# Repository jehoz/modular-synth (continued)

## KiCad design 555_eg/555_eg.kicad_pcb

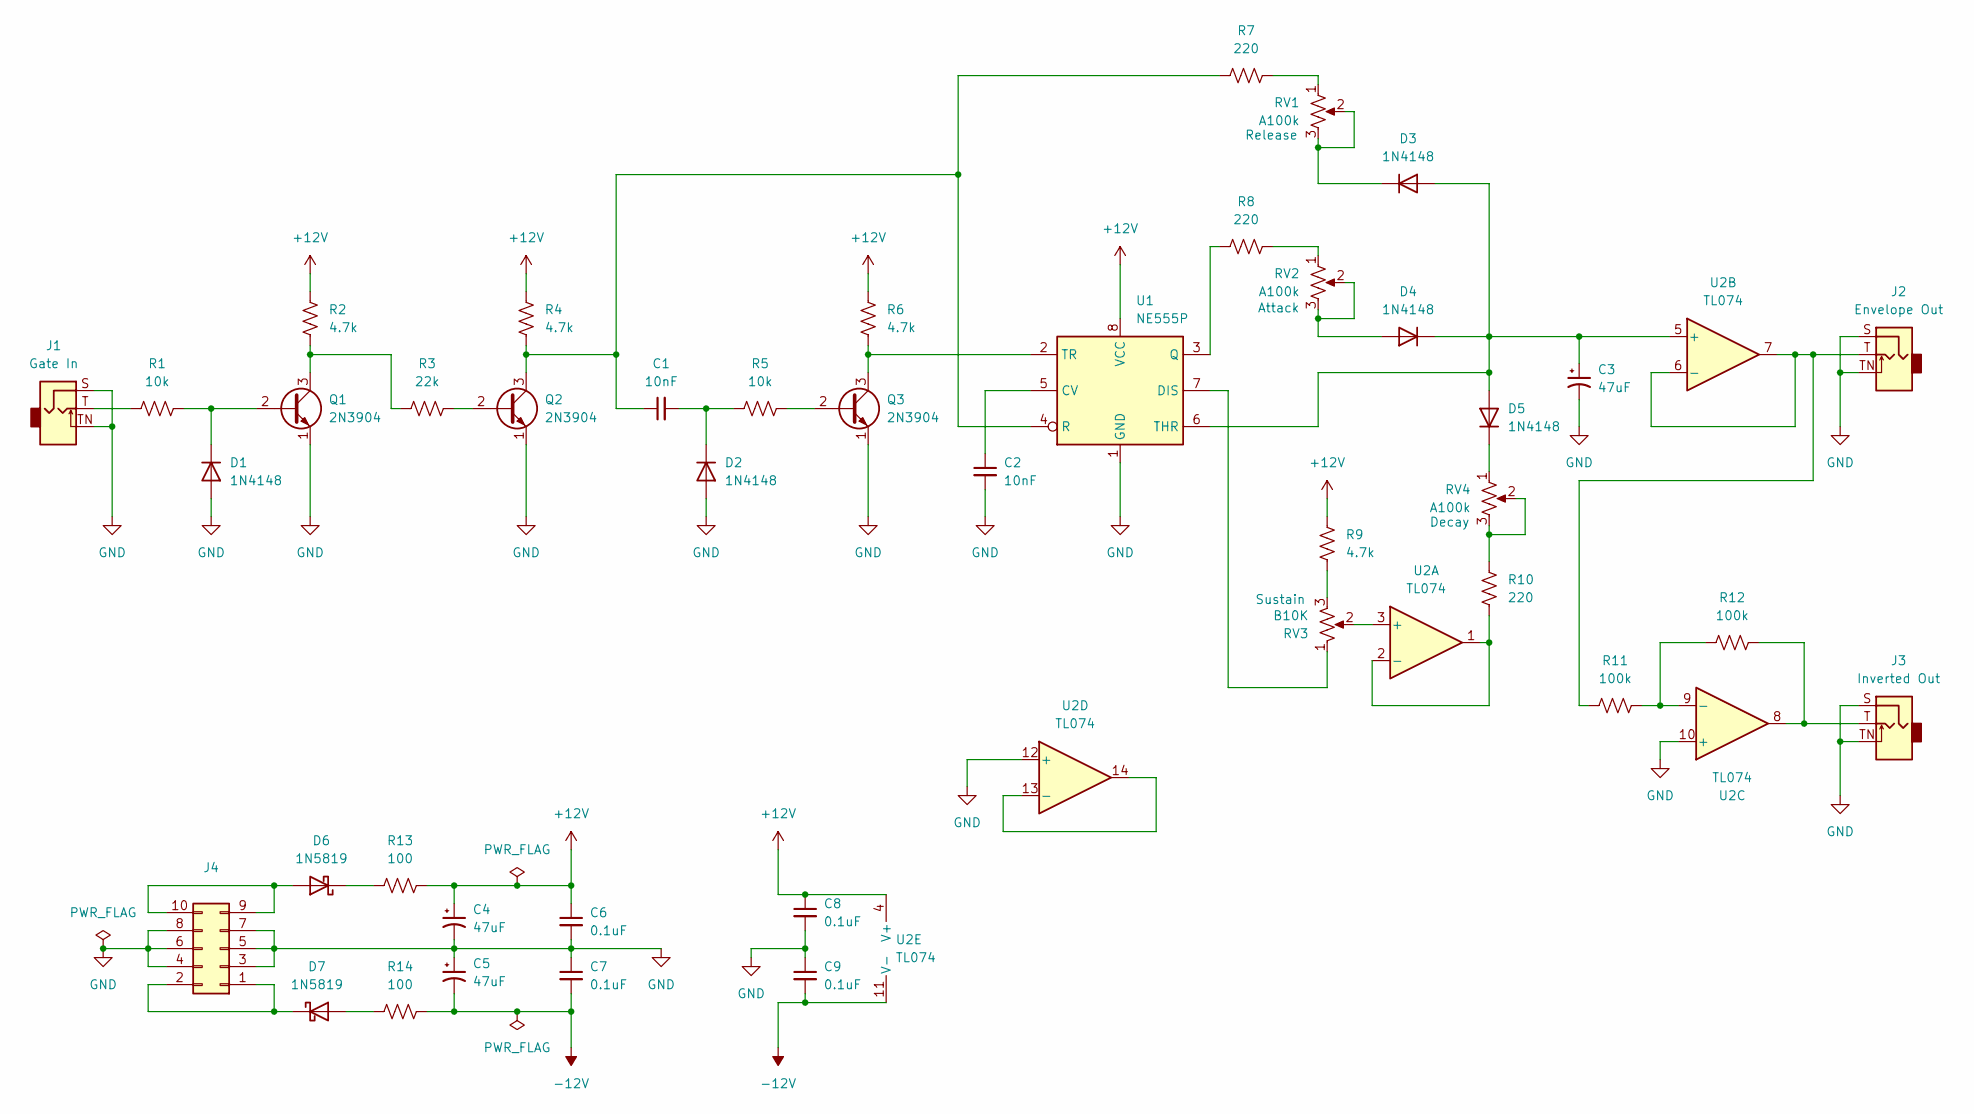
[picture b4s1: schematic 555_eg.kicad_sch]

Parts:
C1, C2: 10nF; C_Rect_L7.2mm_W2.5mm_P5.00mm_FKS2_FKP2_MKS2_MKP2
C3, C4, C5: 47uF; CP_Radial_D6.3mm_P2.50mm
C6, C7, C8, C9: 0.1uF; C_Rect_L7.2mm_W2.5mm_P5.00mm_FKS2_FKP2_MKS2_MKP2
D1, D2, D3, D4, D5: 1N4148; D_DO-35_SOD27_P7.62mm_Horizontal
D6, D7: 1N5819; D_DO-41_SOD81_P10.16mm_Horizontal
J1: Gate In; PinHeader_1x03_P2.54mm_Vertical_AudioJack
J2: Envelope Out; PinHeader_1x03_P2.54mm_Vertical_AudioJack
J3: Inverted Out; PinHeader_1x03_P2.54mm_Vertical_AudioJack
J4: Power Connector; IDC-Header_2x05_P2.54mm_Vertical
Q1, Q2, Q3: 2N3904; TO-92_Inline
R1, R5: 10k; R_Axial_DIN0207_L6.3mm_D2.5mm_P10.16mm_Horizontal
R2, R4, R6, R9: 4.7k; R_Axial_DIN0207_L6.3mm_D2.5mm_P10.16mm_Horizontal
R3: 22k; R_Axial_DIN0207_L6.3mm_D2.5mm_P10.16mm_Horizontal
R7, R8, R10: 220; R_Axial_DIN0207_L6.3mm_D2.5mm_P10.16mm_Horizontal
R11, R12: 100k; R_Axial_DIN0207_L6.3mm_D2.5mm_P10.16mm_Horizontal
R13, R14: 100; R_Axial_DIN0207_L6.3mm_D2.5mm_P10.16mm_Horizontal
RV1, RV2, RV4: A100k; PinHeader_1x03_P2.54mm_Vertical
RV3: B10K; PinHeader_1x03_P2.54mm_Vertical
U1: NE555P; DIP-8_W7.62mm
U2: TL074; DIP-14_W7.62mm_Socket

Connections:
+12V: C4.1, C6.1, C8.1, R2.2, R4.2, R6.2, R9.2, R13.2, U1.8 (VCC), U2.4 (V+)
-12V: C5.2, C7.2, C9.2, R14.2, U2.11 (V-)
GND: C2.2, C3.2, C4.2, C5.1, C6.2, C7.1, C8.2, C9.1, D1.2 (A), D2.2 (A), J1.S, J1.TN, J2.S, J2.TN, J3.S, J3.TN, J4.3, J4.4, J4.5, J4.6, J4.7, J4.8, Q1.1 (E), Q2.1 (E), Q3.1 (E), U1.1 (GND), U2.10 (+), U2.12 (+)
unnamed: D1.1 (K), Q1.2 (B), R1.2
unnamed: C1.2, D2.1 (K), R5.1
unnamed: C3.1, D3.2 (A), D4.1 (K), D5.2 (A), U1.6 (THR), U2.5 (+)
unnamed: D3.1 (K), RV1.2, RV1.3
unnamed: D4.2 (A), RV2.2, RV2.3
unnamed: D5.1 (K), RV4.1
unnamed: D6.2 (A), J4.9, J4.10
unnamed: D6.1 (K), R13.1
unnamed: D7.2 (A), R14.1
unnamed: D7.1 (K), J4.1, J4.2
unnamed: J1.T, R1.1
unnamed: J3.T, R12.2, U2.8
unnamed: Q1.3 (C), R2.1, R3.2
unnamed: Q2.2 (B), R3.1
unnamed: C1.1, Q2.3 (C), R4.1, R7.2, U1.4 (R)
unnamed: Q3.2 (B), R5.2
unnamed: Q3.3 (C), R6.1, U1.2 (TR)
unnamed: R7.1, RV1.1
unnamed: R8.1, RV2.1
unnamed: R9.1, RV3.3
unnamed: R10.1, RV4.2, RV4.3
unnamed: C2.1, U1.5 (CV)
unnamed: RV3.1, U1.7 (DIS)
unnamed: R8.2, U1.3 (Q)
unnamed: RV3.2, U2.3 (+)
unnamed: R10.2, U2.1, U2.2 (-)
unnamed: J2.T, R11.1, U2.6 (-), U2.7
unnamed: R11.2, R12.1, U2.9 (-)
unnamed: U2.13 (-), U2.14

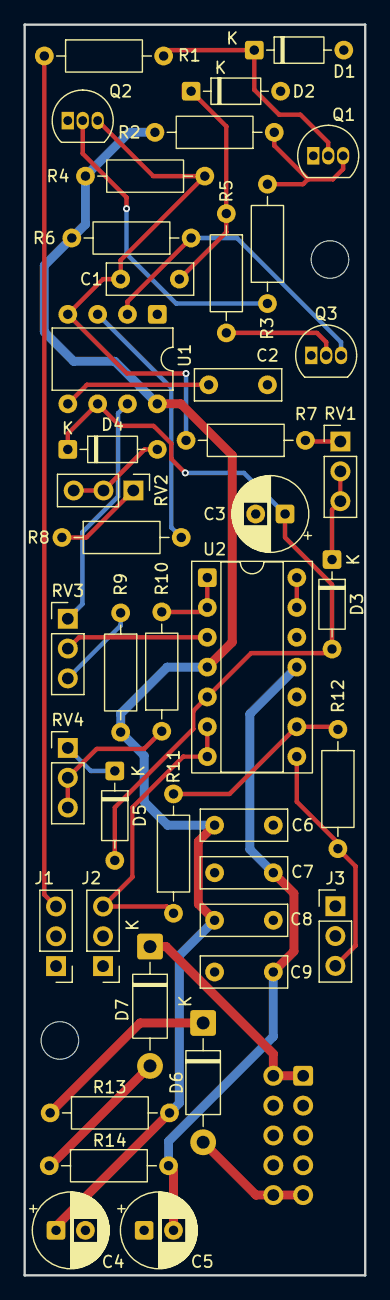
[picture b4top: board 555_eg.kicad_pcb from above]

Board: 2 copper layers, 29.0 x 106.5 mm, 43 parts (1 on the bottom side), 32 nets.

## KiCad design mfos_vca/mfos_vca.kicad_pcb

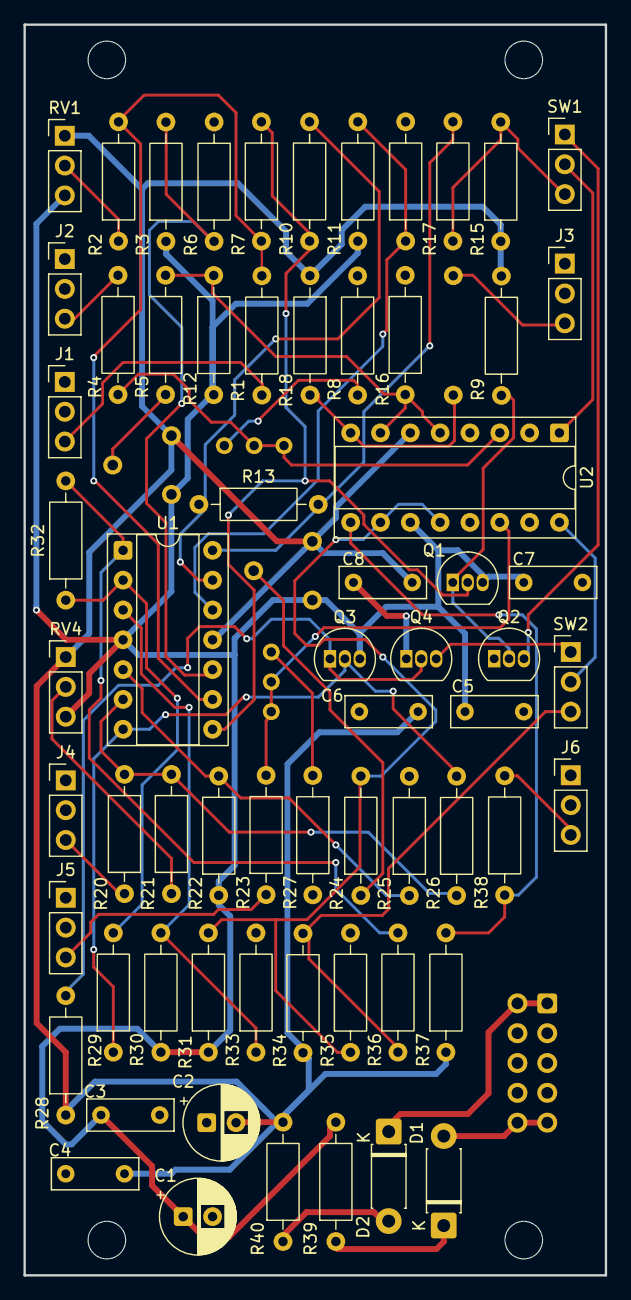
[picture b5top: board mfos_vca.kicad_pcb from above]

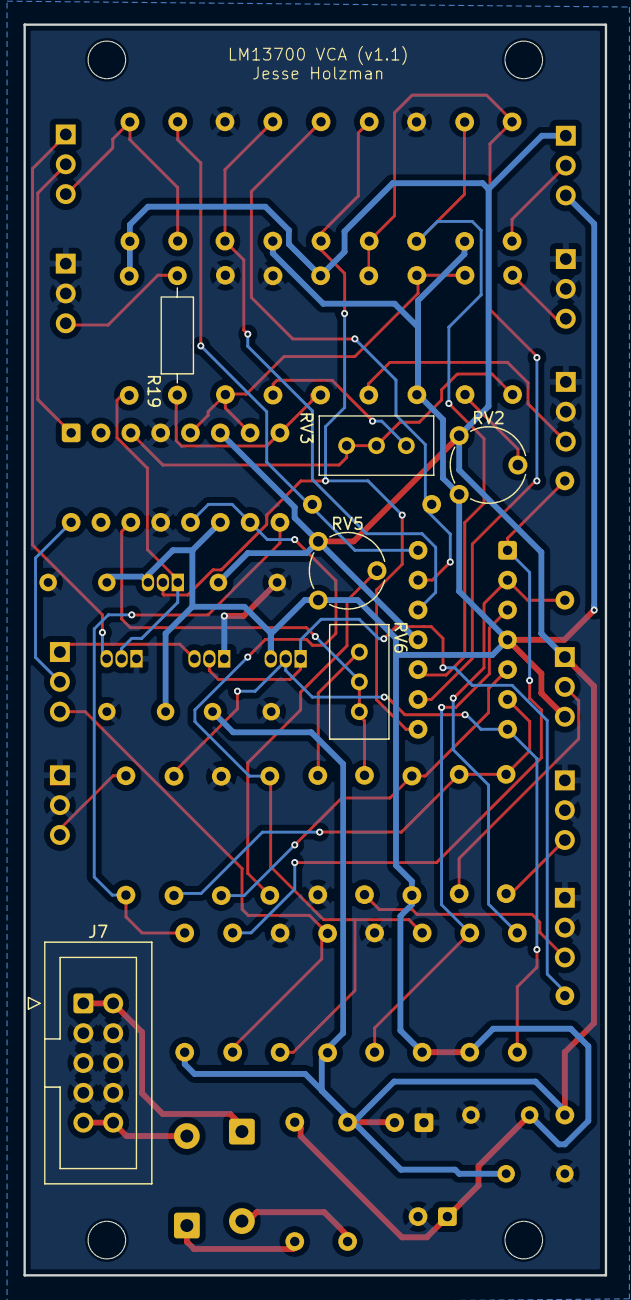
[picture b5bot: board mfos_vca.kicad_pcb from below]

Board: 2 copper layers, 49.5 x 106.5 mm, 71 parts (6 on the bottom side), 45 nets.

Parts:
C1, C2: 47uF; CP_Radial_D6.3mm_P2.50mm
C3, C4, C5, C6, C7, C8: 0.1uF; C_Rect_L7.2mm_W2.5mm_P5.00mm
D1, D2: 1N5819; D_DO-41_SOD81_P7.62mm_Horizontal
J1: CV A; PinHeader_1x03_P2.54mm_Vertical_AudioJack
J2: Signal In A; PinHeader_1x03_P2.54mm_Vertical_AudioJack
J3: Signal Out A; PinHeader_1x03_P2.54mm_Vertical_AudioJack
J4: CV B; PinHeader_1x03_P2.54mm_Vertical_AudioJack
J5: Signal In B; PinHeader_1x03_P2.54mm_Vertical_AudioJack
J6: Signal Out B; PinHeader_1x03_P2.54mm_Vertical_AudioJack
J7: Conn_02x05_Odd_Even; IDC-Header_2x05_P2.54mm_Vertical
Q1, Q3: 2N3904; TO-92_Inline
Q2, Q4: 2N3906; TO-92_Inline
R1, R2, R3, R4, R11, R13, R20, R21, R22, R23, R30, R32: 100k; R_Axial_DIN0207_L6.3mm_D2.5mm_P10.16mm_Horizontal
R5, R24: 2M; R_Axial_DIN0207_L6.3mm_D2.5mm_P10.16mm_Horizontal
R6, R7, R10, R25, R26, R29: 2k; R_Axial_DIN0207_L6.3mm_D2.5mm_P10.16mm_Horizontal
R8, R27: 150 ohm; R_Axial_DIN0207_L6.3mm_D2.5mm_P10.16mm_Horizontal
R9, R28: 120k; R_Axial_DIN0207_L6.3mm_D2.5mm_P10.16mm_Horizontal
R12, R31: 470k; R_Axial_DIN0207_L6.3mm_D2.5mm_P10.16mm_Horizontal
R14, R33: 470 ohm; R_Axial_DIN0207_L6.3mm_D2.5mm_P10.16mm_Horizontal
R15, R34: 20k; R_Axial_DIN0207_L6.3mm_D2.5mm_P10.16mm_Horizontal
R16, R35: 47k; R_Axial_DIN0207_L6.3mm_D2.5mm_P10.16mm_Horizontal
R17, R36: 30k; R_Axial_DIN0207_L6.3mm_D2.5mm_P10.16mm_Horizontal
R18, R37: 4.7k; R_Axial_DIN0207_L6.3mm_D2.5mm_P10.16mm_Horizontal
R19, R38: 1k; R_Axial_DIN0207_L6.3mm_D2.5mm_P10.16mm_Horizontal
R39, R40: 10 ohm; R_Axial_DIN0207_L6.3mm_D2.5mm_P10.16mm_Horizontal
RV1, RV4: 100k; PinHeader_1x03_P2.54mm_Vertical
RV2, RV5: 100k; Potentiometer_Piher_PT-6-V_Vertical
RV3, RV6: 2k; Potentiometer_Bourns_3296W_Vertical
SW1, SW2: SW_SPDT; PinHeader_1x03_P2.54mm_Vertical
U1: TL074; DIP-14_W7.62mm_Socket
U2: LM13700; DIP-16_W7.62mm_Socket

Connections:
+12V: C1.1, C3.1, C5.1, C7.1, Q1.3 (C), Q3.3 (C), R3.1, R11.1, R12.1, R22.1, R30.1, R31.1, R39.2, RV1.3, RV2.1, RV4.3, RV5.1, U1.4 (V+), U2.11 (V+)
-12V: C2.2, C4.2, C6.2, C8.2, R9.1, R15.1, R18.1, R28.1, R34.1, R37.1, R40.2, RV1.1, RV2.3, RV4.1, RV5.3, U1.11 (V-), U2.6 (V-)
GND: C1.2, C2.1, C3.2, C4.1, C5.2, C6.1, C7.2, C8.1, J1.S, J1.TN, J2.S, J2.TN, J3.S, J3.TN, J4.S, J4.TN, J5.S, J5.TN, J6.S, J6.TN, J7.3, J7.4, J7.5, J7.6, J7.7, J7.8, Q2.1 (E), Q4.1 (E), R6.2, R8.2, R14.2, R16.2, R25.2, R27.2, R33.2, R35.2, U2.4 (-), U2.13 (-)
unnamed: D1.2 (A), J7.9, J7.10
unnamed: D1.1 (K), R39.1
unnamed: D2.2 (A), R40.1
unnamed: D2.1 (K), J7.1, J7.2
unnamed: J1.T, R1.1
unnamed: J2.T, R4.1
unnamed: J3.T, R19.2
unnamed: J4.T, R20.1
unnamed: J5.T, R23.1
unnamed: J6.T, R38.2
unnamed: Q1.2 (B), R7.2, R10.1, U1.8
unnamed: Q1.1 (E), Q2.2 (B), R9.2
unnamed: Q2.3 (C), SW1.1 (A)
unnamed: Q3.2 (B), R26.2, R29.1, U1.7
unnamed: Q3.1 (E), Q4.2 (B), R28.2
unnamed: Q4.3 (C), SW2.1 (A)
unnamed: R2.1, RV1.2
unnamed: R5.1, RV2.2
unnamed: R8.1, RV3.3
unnamed: R5.2, R12.2, R16.1, U2.5, U2.7
unnamed: R13.2, R17.2, U1.14
unnamed: R18.2, R19.1, U2.8
unnamed: R21.1, RV4.2
unnamed: R24.1, RV5.2
unnamed: R24.2, R31.2, R35.1, U2.10, U2.12
unnamed: R27.1, RV6.3
unnamed: R32.2, R36.2, U1.1
unnamed: R37.2, R38.1, U2.9
unnamed: SW1.2 (B), U2.1
unnamed: R15.2, R17.1, SW1.3 (C)
unnamed: SW2.2 (B), U2.16
unnamed: R34.2, R36.1, SW2.3 (C)
unnamed: R30.2, R33.1, U1.3 (+)
unnamed: R29.2, R32.1, U1.2 (-)
unnamed: R22.2, R25.1, U1.5 (+)
unnamed: R20.2, R21.2, R26.1, U1.6 (-)
unnamed: R3.2, R6.1, U1.10 (+)
unnamed: R1.2, R2.2, R7.1, U1.9 (-)
unnamed: R11.2, R14.1, U1.12 (+)
unnamed: R10.2, R13.1, U1.13 (-)
unnamed: R23.2, RV6.1, RV6.2, U2.14 (+)
unnamed: R4.2, RV3.1, RV3.2, U2.3 (+)

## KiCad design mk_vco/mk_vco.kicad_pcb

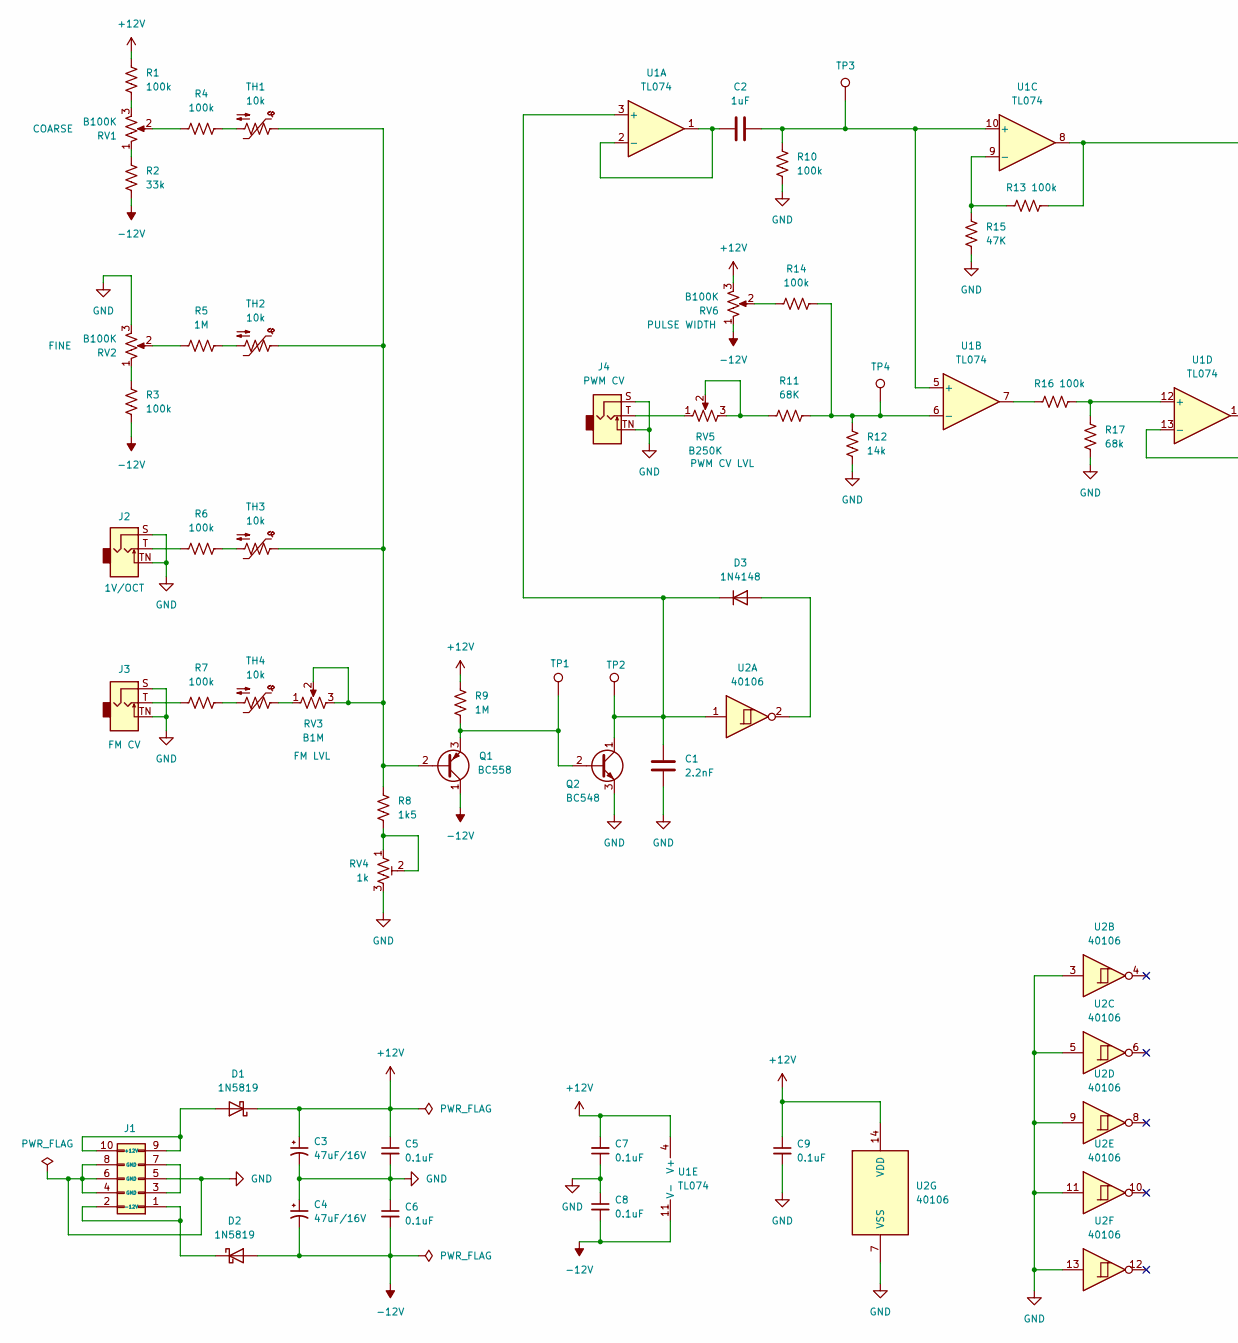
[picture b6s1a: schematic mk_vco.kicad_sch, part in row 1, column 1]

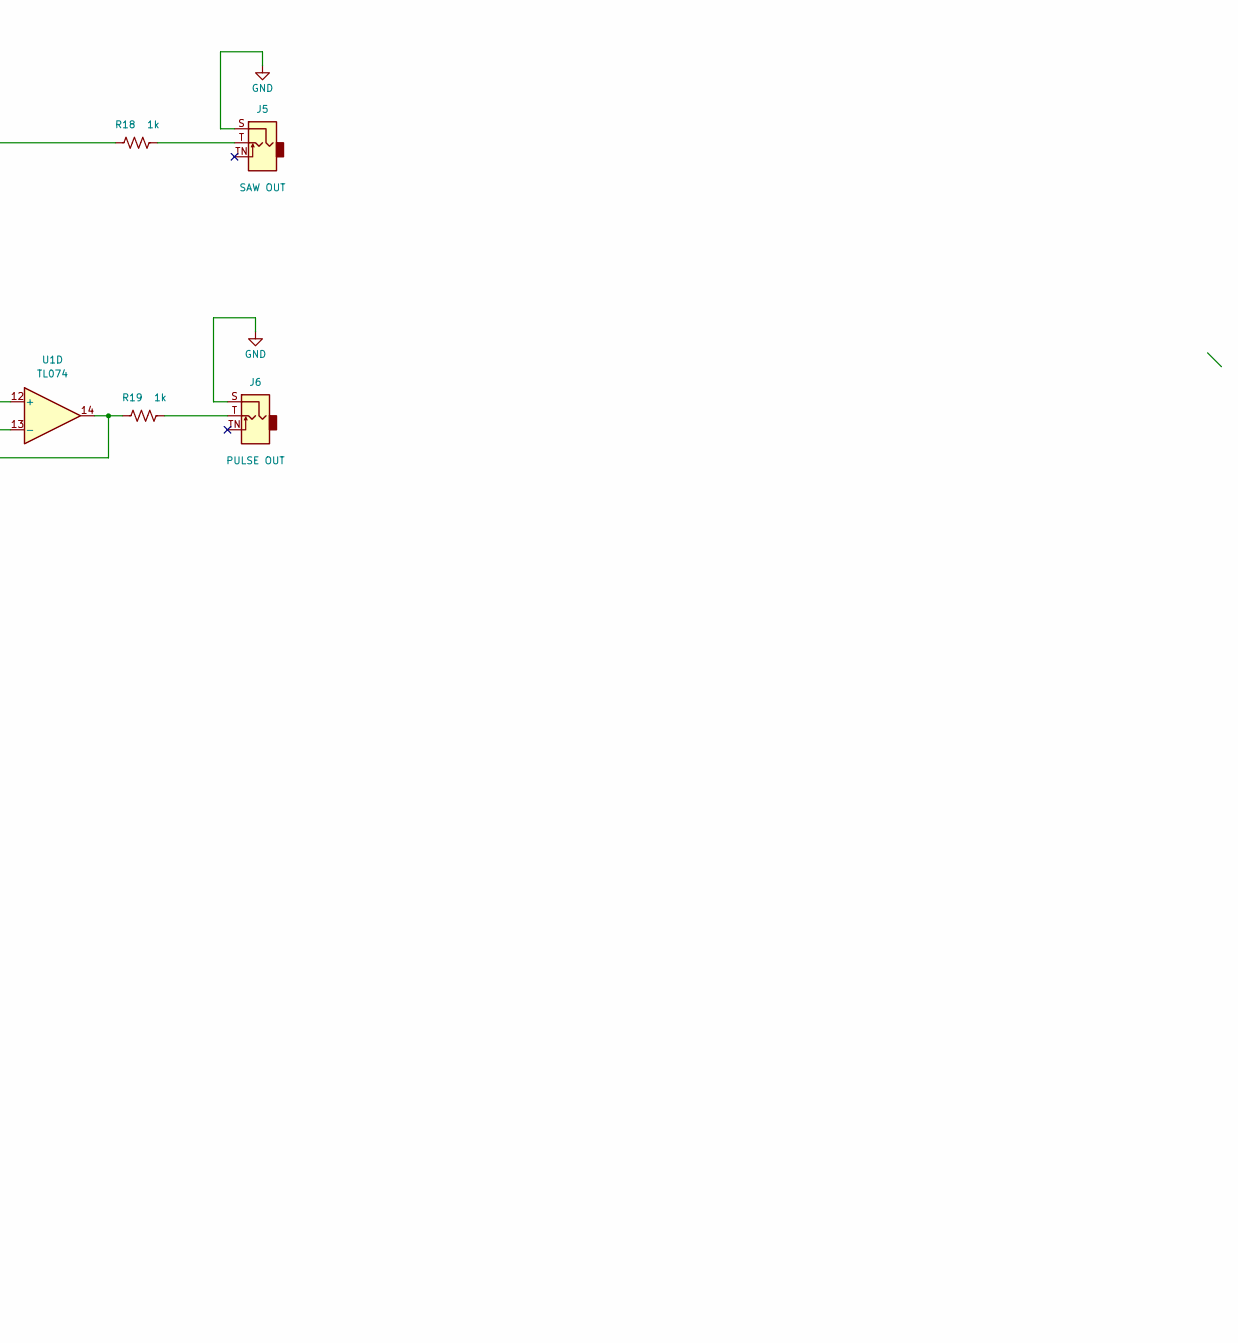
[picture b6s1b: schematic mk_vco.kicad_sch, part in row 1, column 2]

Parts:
C1: 2.2nF; C_Rect_L7.0mm_W2.5mm_P5.00mm
C2: 1uF; C_Rect_L7.0mm_W6.0mm_P5.00mm
C3, C4: 47uF_5x5.3_16V; CP_Radial_D6.3mm_P2.50mm; Part Number VE-470M1CTR-0505; JLCPCB ID C134798
C5, C6, C7, C8, C9: 0.1uF_0603_16V; C_Disc_D8.0mm_W2.5mm_P5.00mm; Part Number 0603YC104KAT2A; JLCPCB ID C14663
D1, D2: 1N5819; D_DO-41_SOD81_P10.16mm_Horizontal
D3: 1N4148; D_DO-35_SOD27_P7.62mm_Horizontal
J1: Conn_02x05_Odd_Even; IDC-Header_2x05_P2.54mm_Vertical
J2: 1V/OCT; Jack_3.5mm_QingPu_WQP-PJ398SM_Vertical_CircularHoles
J3: FM CV; Jack_3.5mm_QingPu_WQP-PJ398SM_Vertical_CircularHoles
J4: PWM CV; Jack_3.5mm_QingPu_WQP-PJ398SM_Vertical_CircularHoles
J5: SAW OUT; Jack_3.5mm_QingPu_WQP-PJ398SM_Vertical_CircularHoles
J6: PULSE OUT; Jack_3.5mm_QingPu_WQP-PJ398SM_Vertical_CircularHoles
Q1: BC558; TO-92_Inline
Q2: BC548; TO-92_Inline
R1, R3, R4, R6, R7, R10, R13, R14, R16: 100k; R_Axial_DIN0207_L6.3mm_D2.5mm_P10.16mm_Horizontal_VALUEINSI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
R2: 33k; R_Axial_DIN0207_L6.3mm_D2.5mm_P10.16mm_Horizontal_VALUEINSI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
R5, R9: 1M; R_Axial_DIN0207_L6.3mm_D2.5mm_P10.16mm_Horizontal_VALUEINSI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
R8: 1k5; R_Axial_DIN0207_L6.3mm_D2.5mm_P10.16mm_Horizontal_VALUEINSI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
R11: 68K; R_Axial_DIN0207_L6.3mm_D2.5mm_P10.16mm_Horizontal_VALUEINSI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
R12: 14k; R_Axial_DIN0207_L6.3mm_D2.5mm_P10.16mm_Horizontal_VALUEINSI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
R15: 47K; R_Axial_DIN0207_L6.3mm_D2.5mm_P10.16mm_Horizontal_VALUEINSI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
R17: 68k; R_Axial_DIN0207_L6.3mm_D2.5mm_P10.16mm_Horizontal_VALUEINSI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
R18, R19: 1k; R_Axial_DIN0207_L6.3mm_D2.5mm_P10.16mm_Horizontal_VALUEINSI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
RV1, RV2, RV6: B100K; Potentiometer_Alpha_RD901F-40-00D_Single_Vertical
RV3: B1M; Potentiometer_Alpha_RD901F-40-00D_Single_Vertical
RV4: 1k; Potentiometer_Bourns_3296W_Vertical
RV5: B250K; Potentiometer_Alpha_RD901F-40-00D_Single_Vertical
TH1, TH2, TH3, TH4: 10k; C_Disc_D4.3mm_W1.9mm_P5.00mm_VALUEINSIDE
TP1, TP2, TP3, TP4: TestPoint; TestPoint_Plated_Hole_D2.0mm
U1: TL074; DIP-14_W7.62mm
U2: 40106; DIP-14_W7.62mm

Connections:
+12V: C3.1, C5.1, C7.2, C9.1, D1.1 (K), R1.1, R9.2, RV6.3, U1.4 (V+), U2.14 (VDD)
-12V: C4.2, C6.2, C8.2, D2.2 (A), Q1.1 (C), R2.2, R3.2, RV6.1, U1.11 (V-)
unnamed: D1.2 (A), J1.9, J1.10
unnamed: D2.1 (K), J1.1, J1.2
unnamed: D3.2 (A), U2.2
unnamed: C1.1, D3.1 (K), Q2.1 (C), TP2.1, U1.3 (+), U2.1
unnamed: J2.T, R6.2
unnamed: J3.T, R7.2
unnamed: J4.T, RV5.1
unnamed: J5.T, R18.1
unnamed: J6.T, R19.1
unnamed: Q1.2 (B), R8.1, RV3.2, RV3.3, TH1.1, TH2.1, TH3.1
unnamed: Q1.3 (E), Q2.2 (B), R9.1, TP1.1
unnamed: R1.2, RV1.3
unnamed: R2.1, RV1.1
unnamed: R3.1, RV2.1
unnamed: R4.1, TH1.2
unnamed: R4.2, RV1.2
unnamed: R5.1, TH2.2
unnamed: R5.2, RV2.2
unnamed: R6.1, TH3.2
unnamed: R7.1, TH4.2
unnamed: R8.2, RV4.1, RV4.2
unnamed: R11.2, RV5.2, RV5.3
unnamed: R13.1, R18.2, U1.8
unnamed: R14.2, RV6.2
unnamed: R16.2, U1.7
unnamed: RV3.1, TH4.1
unnamed: C2.1, U1.1, U1.2 (-)
unnamed: C2.2, R10.2, TP3.1, U1.5 (+), U1.10 (+)
unnamed: R11.1, R12.2, R14.1, TP4.1, U1.6 (-)
unnamed: R13.2, R15.2, U1.9 (-)
unnamed: R16.1, R17.2, U1.12 (+)
unnamed: R19.2, U1.13 (-), U1.14

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
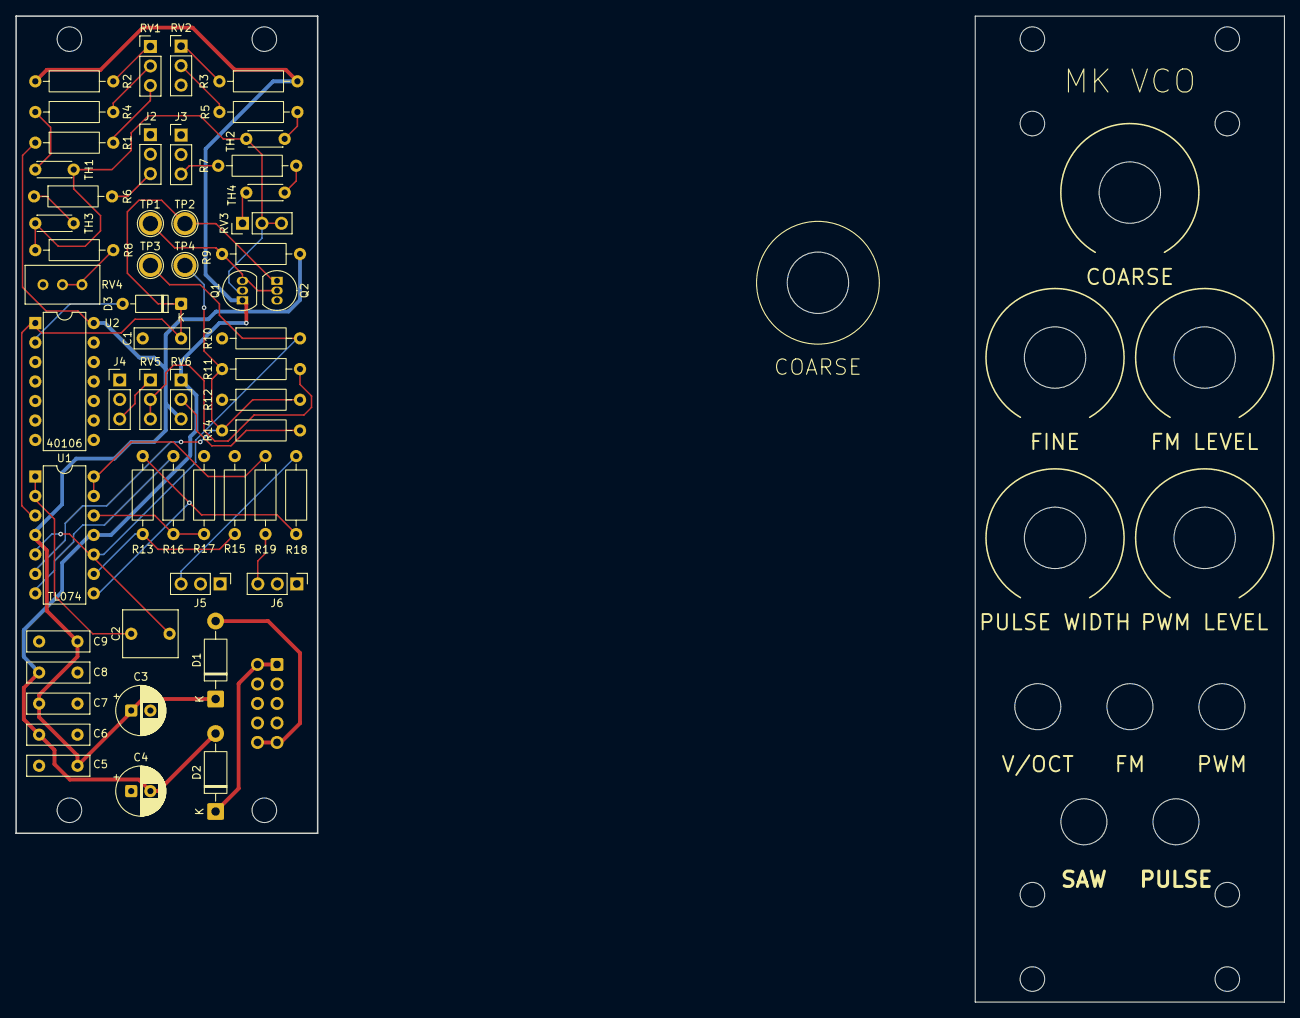
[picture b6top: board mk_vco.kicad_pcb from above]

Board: 2 copper layers, 165.2 x 128.4 mm, 55 parts (1 on the bottom side), 35 nets.

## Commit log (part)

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2025-11-21 Add everything
2025-11-21 code: ai slop docker
2025-12-31 reorganize
2025-12-31 Add power supply schematic
2025-12-31 Add all kicad tempfiles to gitignore
2026-01-08 add power supply stripboard layout image
2026-01-12 Start schematic for mfos vca
2026-01-13 Mostly finish VCA-A schematic
2026-01-14 Add schematic for second VCA
2026-01-15 Finish VCA schematic
2026-01-16 Assign footprints
2026-01-19 some progress on vca pcb
2026-01-21 Remove secondary CV input per VCA, some more panel progress
2026-01-21 Add local footprint library for audio jack 3-pin header
2026-01-21 More progress, got rid of second cv input
2026-01-22 vca pcb progress from last night
2026-01-26 Finished placing components on vca board
2026-01-28 not actually sure what these changes are, but going to commit them anyway
2026-01-30 Almost done all of the tracks in vca pcb, fix the custom library footprint
2026-01-31 All DRC errors resolved :)
2026-01-31 split out panel into its own pcb file
2026-02-02 Finalize panel and pcb for VCA, add gerbers
2026-03-13 fix a couple stupid mistakes in schematic
2026-03-16 update vca pcb with schematic fixes
2026-03-17 fix pcb holes
2026-04-29 Finish schematic for envelope generator
2026-05-18 Start working on PCB for envelope generator
2026-05-22 Finish eg pcb, almost done panel
2026-05-24 get rid of gerber files in repo
2026-05-24 final changes to 555 EG and fixed VCA pcb before ordering
